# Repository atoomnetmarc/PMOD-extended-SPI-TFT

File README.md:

This is a extended SPI PMOD board and holds a [1.8 inch SPI TFT screen with SD-card](http://www.lcdwiki.com/1.8inch_SPI_Module_ST7735S_SKU:MSP1804).

When not working with the ST7735S driver, try the S6D02A1 driver. It seems that the S6D02A1 was used on older 1.8 TFT modules (with blue tab).

*Status*: confirmed working.

Note: lay down C1 (if top hits TFT module when mounting upright).

My [Kicad library](https://github.com/atoomnetmarc/ATOOMNETKICAD) is used in this project.

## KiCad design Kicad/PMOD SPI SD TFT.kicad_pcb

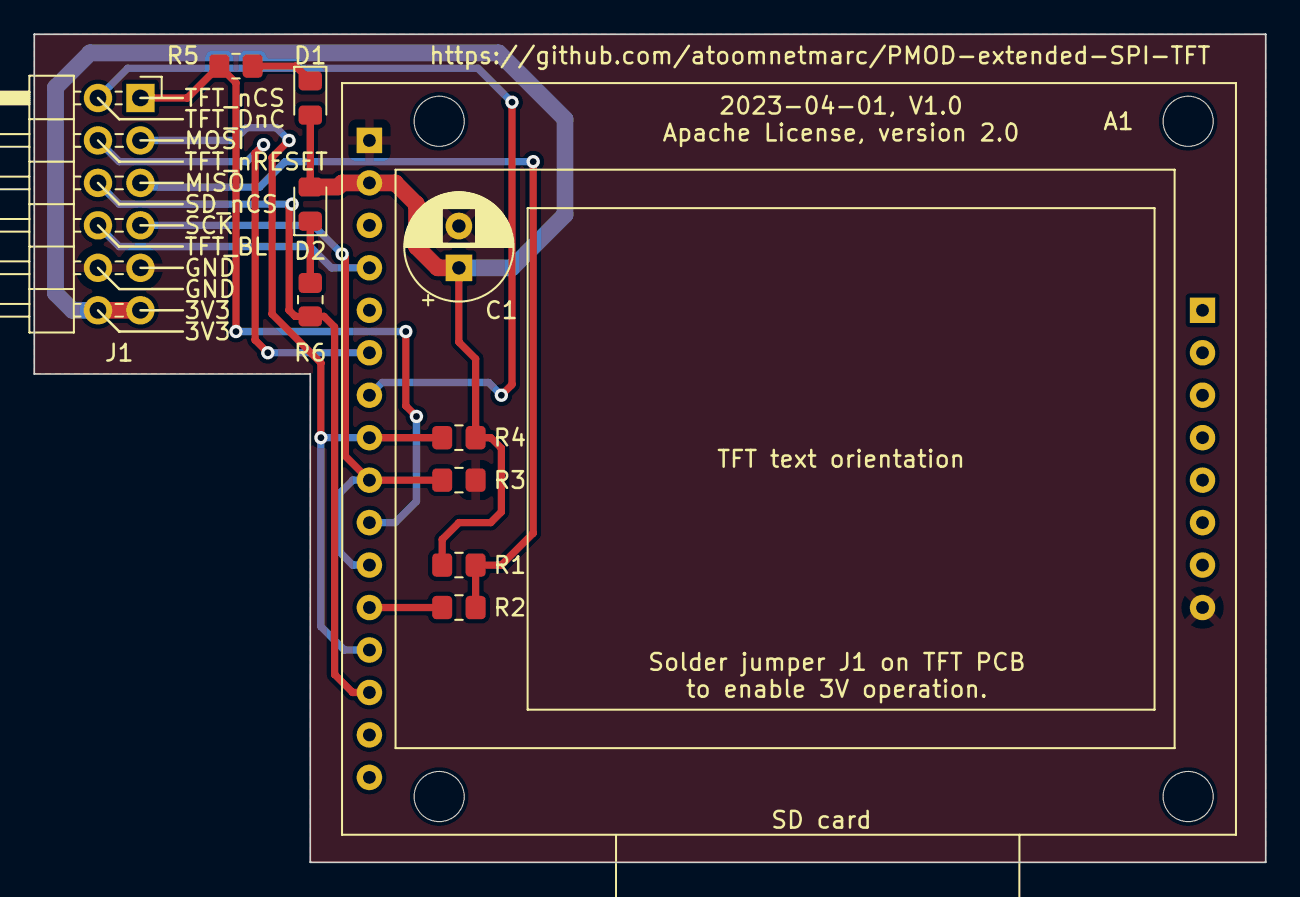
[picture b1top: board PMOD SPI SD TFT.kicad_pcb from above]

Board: 2 copper layers, 73.7 x 49.5 mm, 11 parts (0 on the bottom side), 13 nets.

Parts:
A1: MSP1804; Module_TFT_1.8_160x128
C1: 33uF 16V; CP_Radial_D6.3mm_P2.50mm
D1, D2: Blue; LED_0805_2012Metric_Pad1.15x1.40mm_HandSolder
J1: Pmod peripheral SPI; PinHeader_2x06_P2.54mm_Horizontal_Top_Bottom
R1, R3, R4: 10k; R_0805_2012Metric_Pad1.20x1.40mm_HandSolder
R2: 100R; R_0805_2012Metric_Pad1.20x1.40mm_HandSolder
R5, R6: 1k; R_0805_2012Metric_Pad1.20x1.40mm_HandSolder

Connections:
+3V3: A1.2L (VCC), C1.1, D1.2 (A), D2.2 (A), J1.6 (VCC), J1.12 (VCC), R1.1, R4.1
GND: A1.1L (GND), A1.8R (GND), C1.2, J1.5 (GND), J1.11 (GND), R3.2
MISO: J1.3 (MISO), R1.2, R2.1
MOSI: A1.8L (TFT_DIN), A1.13L (SD_MOSI), J1.2 (MOSI), R4.2
unnamed: A1.12L (SD_MISO), R2.2
unnamed: D1.1 (K), R5.1
unnamed: D2.1 (K), R6.1
SCK: A1.9L (TFT_CLK), A1.11L (SD_CLK), J1.4 (SCK), R3.1
SD_~CS: A1.14L (SD_~CS), J1.9 (~CS2/GPIO), R6.2
TFT_BL: A1.4L (TFT_BL), J1.10 (~CS3/GPIO)
TFT_D~C: A1.7L (TFT_D~C), J1.7 (~INT/GPIO)
TFT_~CS: A1.10L (TFT_~CS), J1.1 (~CS), R5.2
TFT_~RST: A1.6L (TFT_~RST), J1.8 (~RESET/GPIO)

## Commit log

2023-04-02 First version.
2023-04-08 Add note about S6D02A1 driver that could be used instead of ST7735S.
2023-05-02 Soldered
2024-09-28 It works!
2026-01-23 Add CONTRIBUTING.md

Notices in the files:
Kicad/PMOD SPI SD TFT.kicad_pcb:
Apache License, version 2.0
README.md:
License: Apache 2.0
